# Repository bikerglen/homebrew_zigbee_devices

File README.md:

# homebrew_zigbee_devices

First up: nRF52840-based four-input sleepy end device

Second up: nRF52840-based hall effect contact sensor sleepy end device

1. Install nRF plugins for Visual Studio Code
2. Use the plugin to install version 2.5.1 of the toolchain and sdk
3. Add custom board definition files
4. Add the zigbee_switch_v2 and zigbee_contact_v1 directories as applications.
5. For each application, create a build using the corresponding custom board.
6. Build and flash each application's build.
7. Install four-input.js as a custom handler in zigbee2mqtt.

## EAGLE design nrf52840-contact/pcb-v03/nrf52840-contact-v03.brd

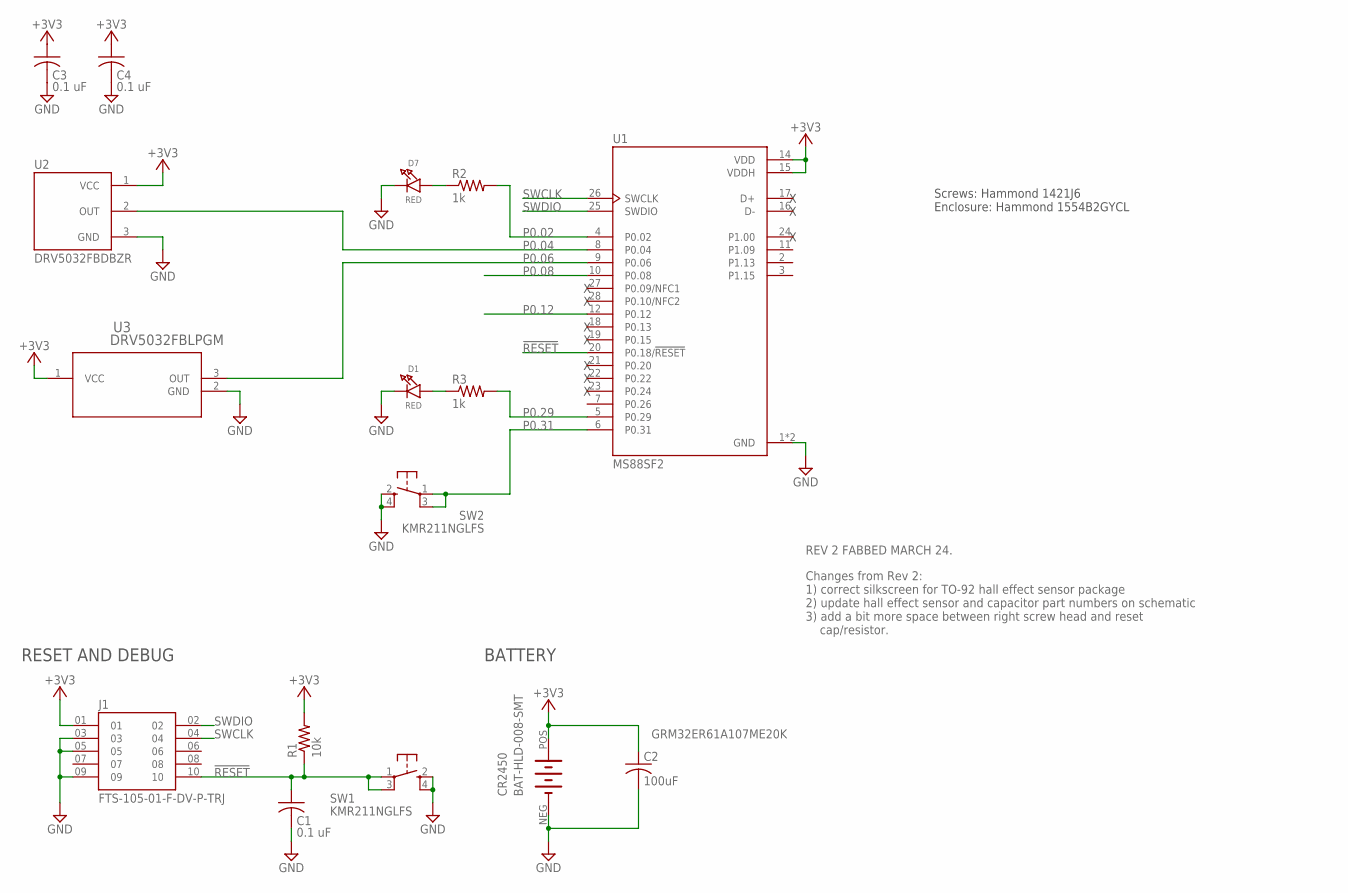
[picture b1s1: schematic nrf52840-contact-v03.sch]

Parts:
C1, C3, C4: 0.1 uF; C0603K
C2: 100uF; C1210K
CR2450: BAT-HLD-008-SMT
D1, D7: RED; CHIPLED_0805_NOOUTLINE
J1: FTS-105-01-F-DV-P-TRJ; SAMTEC_FTS-105-01-F-DV-P-TR
R1: 10k; R0603
R2, R3: 1k; R0603
SW1, SW2: KMR211NGLFS; KMR2
U1: MS88SF2; XCVR_MS88SF2
U2: DRV5032FBDBZR; SOT95P237X112-3N
U3: DRV5032FBLPGM; TO-92-3_DRV5032A_4X3P15_TEX

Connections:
!RESET: C1.1, J1.10, R1.1, SW1.1, SW1.3 (P1), U1.20 (P0.18/!RESET)
+3V3: C2.1, C3.1, C4.1, CR2450.POS (+), J1.01, R1.2, U1.14 (VDD), U1.15 (VDDH), U2.1 (VCC), U3.1 (VCC)
GND: C1.2, C2.2, C3.2, C4.2, CR2450.NEG (-), D1.C, D7.C, J1.03, J1.05, J1.09, SW1.2 (S), SW1.4 (S1), SW2.2 (S), SW2.4 (S1), U1.1 (GND), U1.13 (GND), U2.3 (GND), U3.2 (GND)
unnamed: D7.A, R2.1
unnamed: D1.A, R3.1
P0.02: R2.2, U1.4 (P0.02)
P0.04: U1.8 (P0.04), U2.2 (OUT)
P0.06: U1.9 (P0.06), U3.3 (OUT)
P0.08: U1.10 (P0.08)
P0.12: U1.12 (P0.12)
P0.29: R3.2, U1.5 (P0.29)
P0.31: SW2.1, SW2.3 (P1), U1.6 (P0.31)
SWCLK: J1.04, U1.26 (SWCLK)
SWDIO: J1.02, U1.25 (SWDIO)

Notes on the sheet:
RESET AND DEBUG
BATTERY
Screws: Hammond 1421J6 Enclosure: Hammond 1554B2GYCL
GRM32ER61A107ME20K
REV 2 FABBED MARCH 24.
Changes from Rev 2: 1) correct silkscreen for TO-92 hall effect sensor package 2) update hall effect sensor and capacitor part numbers on schematic 3) add a bit more space between right screw head and reset cap/resistor.

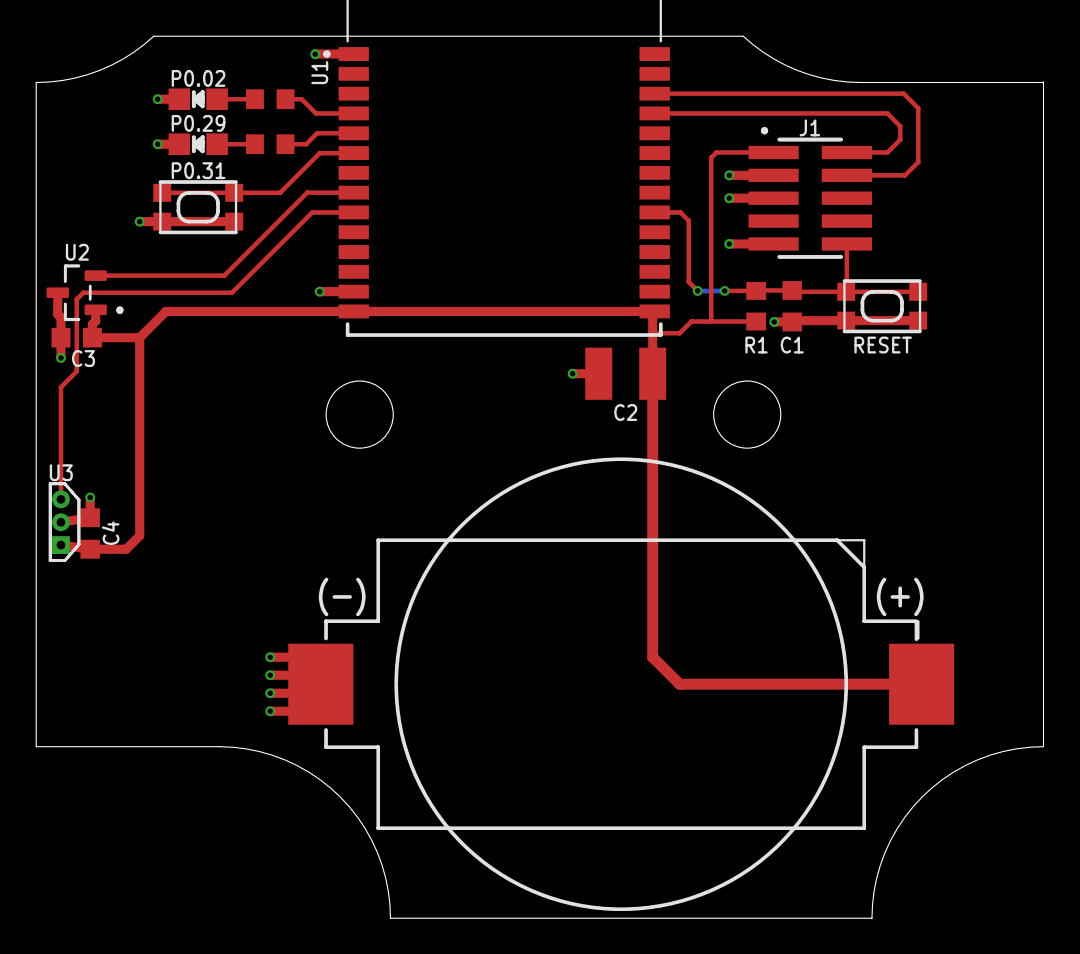
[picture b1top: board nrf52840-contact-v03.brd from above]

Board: 2 copper layers, 56.0 x 49.0 mm, 16 parts (0 on the bottom side), 12 nets.

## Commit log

2024-02-14 test checkin and push
2024-02-14 initial checkin
2024-02-14 add bom
2024-02-15 add eagle pcb files
2024-03-03 add zigbee2mqtt driver for the four-input module
2024-03-03 add board defintion files for Nordic nRF Connect plugin for Visual Studio Code
2024-03-25 add hall effect contact sensor device tree files
2024-03-25 add hall effect contact sensor pcb design files
2024-03-25 add zigbee2mqtt file for hall effec contact sensor
2024-03-25 move four input sensor board files and flatten directory hierarchy
2024-03-25 add software build files
2024-03-25 add contact sensor build files
2024-03-25 add a few instructions
2024-03-25 add space maybe
2024-03-25 more instructions
2024-03-25 add sdk version
2024-04-24 add demo python script to listen to mqtt messages and control lights

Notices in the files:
parts and their libraries:
microbuilder: This work is placed in the public domain, and may be freely used for commercial and non-commercial work with the following conditions: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
COPYRIGHT: Copyright (C) 2024 Ultra Librarian. All rights reserved.
